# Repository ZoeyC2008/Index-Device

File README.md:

# Index Device

All creative credits go to Project Moon, I'm just trying to create the concept in the real world.

Goal: Create a functional prescript device/beeper, similar to what Rien and Sora have. Funationality being that it makes a beep, displays the prescript, and lets the user say that they've completed it (oh, and also unlock your weapons and grant you shin, mang, and E.G.O.).

Use case: I suppose it can be a worse version of the reminders people set on their phones? I'm mostly doing this because Project Moon has been my latest hyperfixation and I wanted to make something in dedication for it. Another use case to be cosplay Rien, Sora, Index Yi Sang, or Index Don Quixote, but I'm not likely to any of those cosplays anytime soon (mostly, I jsut want to cosplay someone with long hair, which none of these characters have).

***

***

## Zine

(The zine can be found under the zine folder.)

## PCB

(The pdf of the PCB is under CAD models/drawings, while the .kicad_pcb is in the schematic folder)

## Code logic

- Semi-randomly send the messages of cryptic nature while beeping
- A short press of the button tells the device that the prescript has been received and displays the given prescript
- A long press of the button tells the device that the prescript has been cleared, dismissing the current prescript, and showing a clear animation

## CAD

CAD! The CAD (and the project in general) was made to resemble this:

***

***

Trying to be thorough, so I'm just going to word for word answer teh questions in Fallout docs:

✓ Short description of what your project is! Highlight what makes it unique

A beeper that sends cryptic instructions (emphasis on cryptic).

***

✓ How do you use it? Be detailed! Others can’t read your mind.

The device will send the instructions randomly, short press the button to show you've received it, and long press to say you've cleared it.

***

✓ Why did you make it? Be personal! Are you solving a problem? Trying to make something smaller than previously thought possible?

I made this because I'm hyperfixating on Project Moon and I think the Index is a really cool faction! (By the will of the City!)

***

***

<details>

<summary> Lore Dump (skippable) </summary>

If you're just here for the project feel free to skip, the rest of the README is just me rambling about Index lore (it's between them and the Ring for which one is my favorite finger).

I need this for myself, but this will contextualize the project better than the intro, or I will sound like a madman, one or the other. So, the Index are one of the five fingers, where the fingers are the five biggest syndicates in the City and between the five of them split up the backstreets (although it might be more between four of them, the Pinky's situation is unclear, but with only 108 seats, it really doesn't feel like they hold ground and if they do, none of the members we see are helping with that: Shiomi and Araya are stuck in the corrider, Ryoshu is on the bus, Jia Qiu, Zilu, and Zigong are doing who knows what, and Lei Heng is hindering any efforts by helping the Thumb).

The Index functions by obeying prescripts, and we have recently learned that prescripts can come in different mediums (paper slips vs device) and they tend to either a very specific direction (e.g. at 3:38 go to an intersection and wave seven times) or it can be ridiculously broad (e.g. kill what you have painted). However, no matter what happens, the prescripts benefit the Index, hence how they became a syndicate.

The Index has an average ranking system compared to the other fingers. As far as we know, the Index's recruiting system is just the prescripts said to indoctrinate X person (it's a cult, that's what they all do). People who initially join the Index are proselytes (it's a cult) who wear a blindfold, but are still given the iconic cloak, and are assigned to a familia where they learn to execute prescripts with other proselytes under a older proxy (it's a cult). Proxies, messengers, and weavers all appear to be on roughly the same level, they just have different duties. Granted, even this hierarchy isn't set in stone as whoever the Will of the City favours on any given day would be doing better (it's a cult), such as how Index Proselyte Faust is able to beat a messenger. Something else notable about the index acting under the Will of the City, is that the Thumb consistantly treats index members with respect under the assumption that they are working under this higher authority.

Rien is weird.He is the only Nursefather to be at the House of Spiders to not be rejected by their own finger (until the very end when he's killed by proxies for disobeying his prescripts). In addition, he's isolated from the proxy-messenger-weaver ecosystem because he receives his prescripts directly from Hermes at a greatly increased frequency (to the point that Rien can hae entire conversations scripted via prescript), all to beome a Roland cosplay of all things. This device is the primary font of inspiration for the project.

The prescripts are fundamentally very exestential, as in thinking about them too hard will make you question whether you have free will. The idea is thus, the prescripts already know whether or not you're going to defy them and are set up in anticipation for that, such as with Yan's whole story where he goes insane trying to comprehend if he has free will or not because the prescript planned for him to make up random ones of his own. I think this is stupid, because you can't approach this question from the perspective of free will, instead you approach it as the prescripts being a perfect predicting machine. If you take it that way, from the prescripts/Will of teh City/Hermes' perspective you do not free will because all your actions are already known as you always have. However, from your own perspective you have thedelusion of free will, ergo you have free will. Putting this into a practical example, Yan thinks he doesn't have free will because the prescripts predicted that he would 'defy' the prescripts, but that defiance was still helping the Index. This caused him to start crashing out and distorting, which only happens when someone's whole worldview is completely shattered. Instead Yan needed to accept that he's playying a losin game that always benefits the Index and the only thing they can choose whether to blindly follow or question the prescripts with no wrong answer.

</details>

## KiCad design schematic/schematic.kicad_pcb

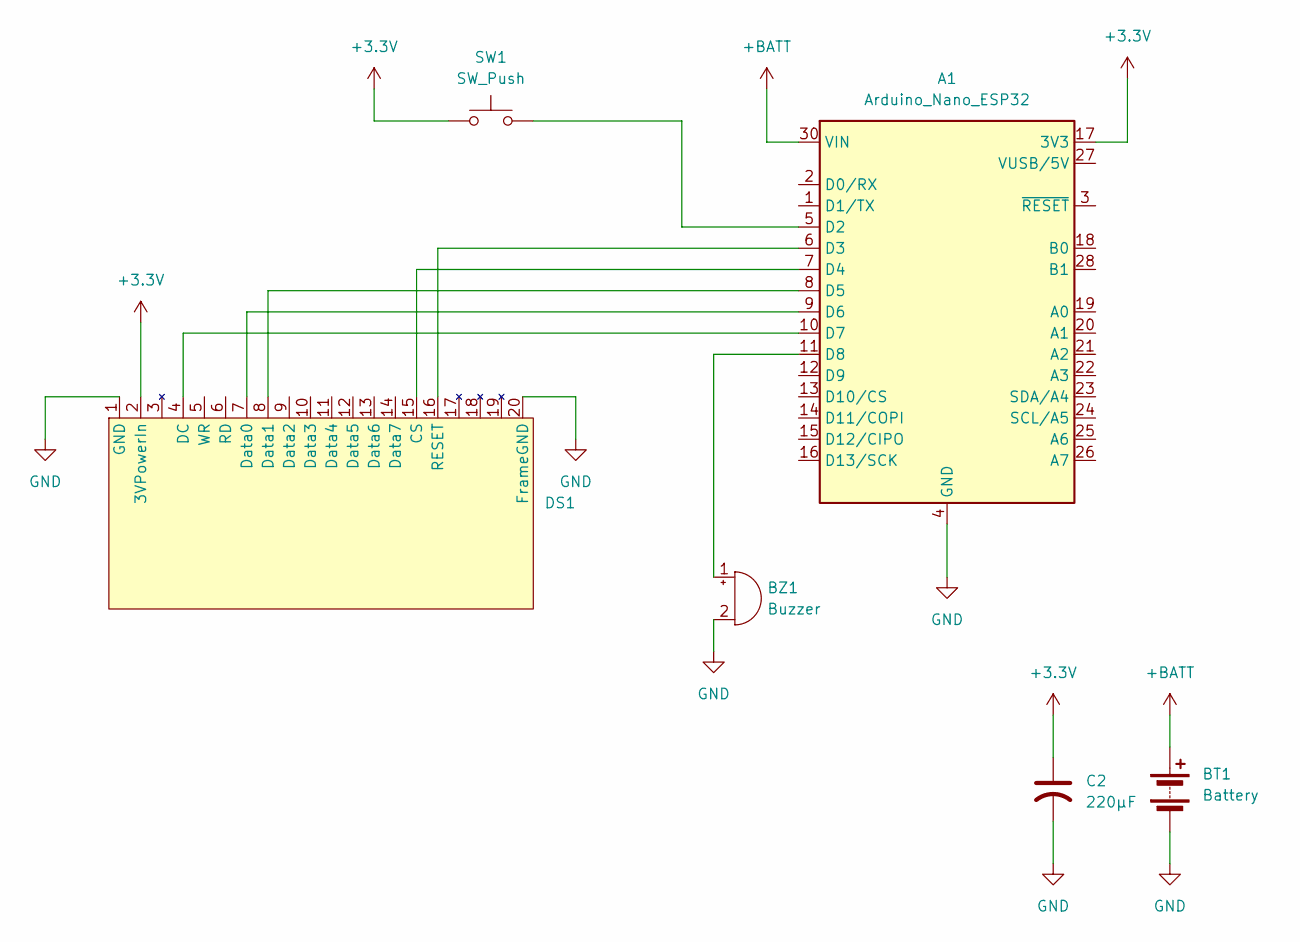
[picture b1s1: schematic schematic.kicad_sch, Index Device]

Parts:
A1: Arduino_Nano_ESP32; Arduino_Nano
BT1: Battery; BatteryHolder_Keystone_2462_2xAA
BZ1: Buzzer; Buzzer_TDK_PS1240P02BT_D12.2mm_H6.5mm
C2: 220μF; C_Radial_D5.0mm_H11.0mm_P2.00mm
DS1: OLED_Graphic_Display_Kit_Adafruit
SW1: SW_Push; SW_PUSH-12mm

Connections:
+3.3V: A1.17 (3V3), C2.1, DS1.2 (3VPowerIn), SW1.1
+BATT: A1.30 (VIN), BT1.1 (+)
GND: A1.4 (GND), A1.29 (GND), BT1.2 (-), BZ1.2 (-), C2.2, DS1.1 (GND), DS1.20 (FrameGND)
unnamed: A1.5 (D2), SW1.2
unnamed: A1.6 (D3), DS1.16 (RESET)
unnamed: A1.7 (D4), DS1.15 (CS)
unnamed: A1.8 (D5), DS1.8 (Data1)
unnamed: A1.9 (D6), DS1.7 (Data0)
unnamed: A1.10 (D7), DS1.4 (DC)
unnamed: A1.11 (D8), BZ1.1 (+)

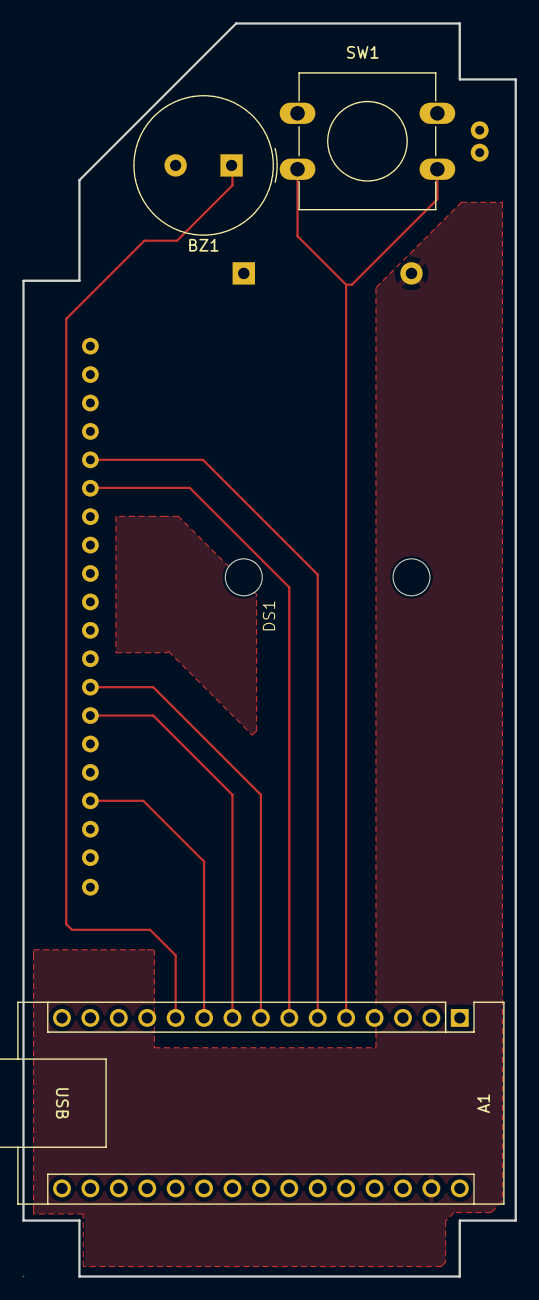
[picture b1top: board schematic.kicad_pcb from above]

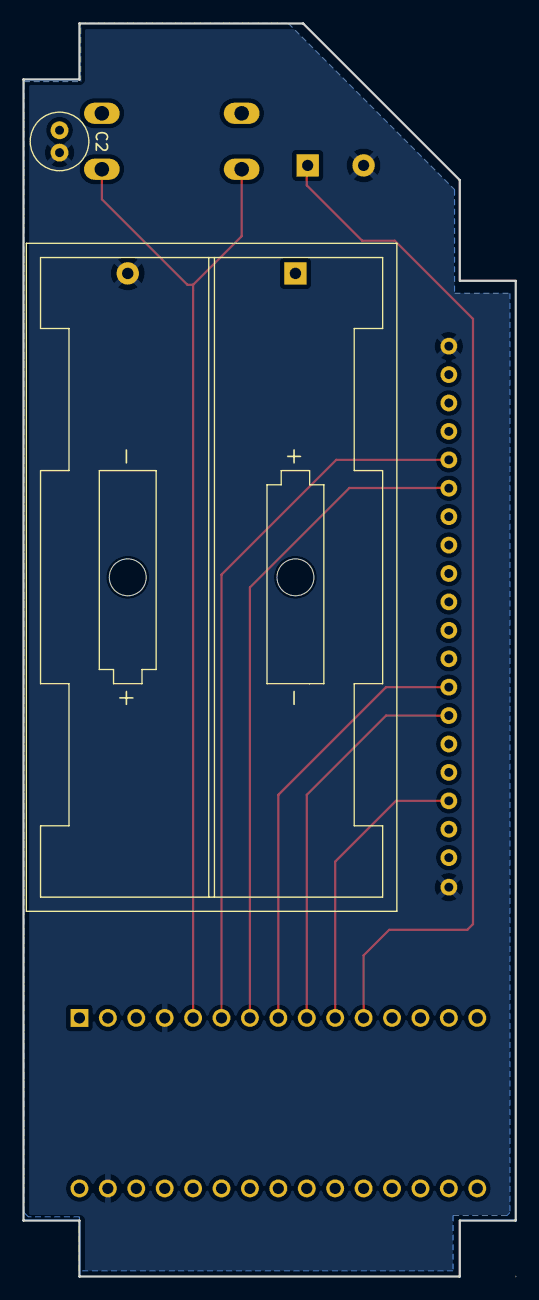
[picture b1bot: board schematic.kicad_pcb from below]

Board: 4 copper layers, 44.0 x 112.0 mm, 6 parts (2 on the bottom side), 10 nets.

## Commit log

2026-06-11 react router
2026-06-12 there's something?
2026-06-12 Shouldn't have done this, but accidentally made the schematic in the docs branch
2026-06-13 schematic and then I started editing the code...
2026-06-14 I think we need to give up on the branches...it's becoming really obvious that it's not working and I'm not really using gitHub for version control (that or it just hasn't gotten bad enough to need t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
2026-06-15 Zine
2026-06-15 Fixed duplicate image
2026-06-15 Added zine pdf
2026-06-15 Fusion files upload
2026-06-16 Fixed fusion
2026-06-16 started firmware
2026-06-16 arduino firmware
2026-06-18 restarting laptop
2026-06-18 finished readme and pcb
2026-06-18 Finished code stuffs?
2026-06-19 not touching fusion, this time for real
2026-06-19 Bill of materials
2026-06-19 fixed schematic edge cuts which was wrong by like 4mm
2026-06-19 renamed bom
2026-06-19 moved bom.csv
